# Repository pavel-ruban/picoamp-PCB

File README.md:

# straddle usb-c connector option (fork changes first 3 images):

pcb|top|bottom|pcb|3d|dev-pcb|dev-3d
--|--|--|--|--|--|--
||||||

* usb c connector https://aliexpress.com/item/1005003274837739.html
* push button soldered on top of the pcb to interact with steamvr dashboard
https://aliexpress.com/item/32622269899.html?sku_id=59394778361

# indexspeakerdacsmol

compact usb-i2s dac using rp2040 and max98360a for powering speakers, like index bmr drivers

* I forgot the silkscreen for usb pins, but they should be clear from below images.
* 0201 components suck to work with.
* intended to use with a usb-c cable, however the CC wire needs 5.1K pull-down to ground which I forgot about

firmware for the device is at https://github.com/sctanf/picoamp

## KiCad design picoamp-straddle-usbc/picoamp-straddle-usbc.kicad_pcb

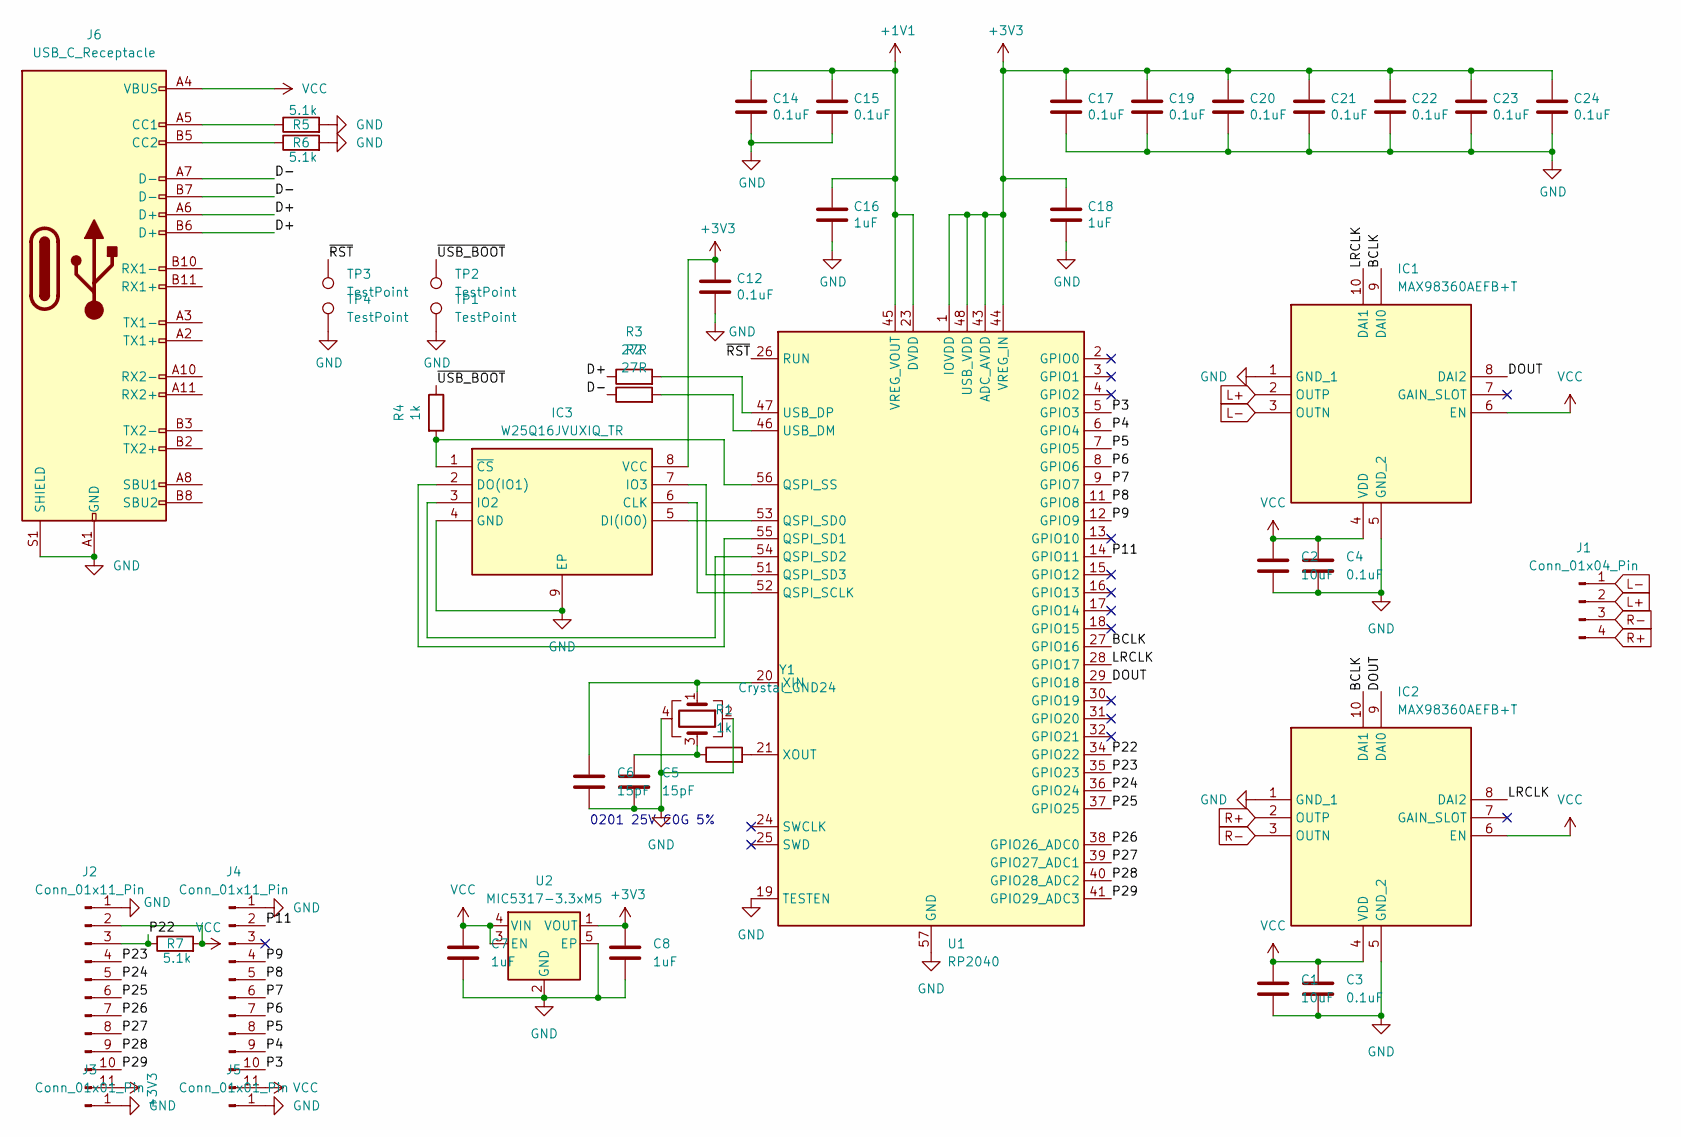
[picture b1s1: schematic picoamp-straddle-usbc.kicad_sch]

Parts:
C1, C2: 10uF; C_0603_1608Metric; Manufacturer_Part_Number GRM188C81A106MA73D; Mouser Part Number 81-GRM188C81A106MA3D
C3, C4: 0.1uF; C_0402_1005Metric; Manufacturer_Part_Number GRM155R61A104KA01J; Mouser Part Number 81-GRM15R61A104KA01J
C5, C6: 15pF; C_0201_0603Metric; Manufacturer_Part_Number GRM0335C1E150JA01D; Mouser Part Number 81-GRM0335C1E150JA1D
C7, C8, C16, C18: 1uF; C_0402_1005Metric; Manufacturer_Part_Number GRM155C81A105KA12J; Mouser Part Number 81-GRM155C81A105KA2J
C12, C14, C15, C17, C19, C20, C21, C22, C23, C24: 0.1uF; C_0201_0603Metric; Manufacturer_Part_Number GRM033C80J104KE15D; Mouser Part Number 81-GRM33C80J104KE15D
IC1, IC2: MAX98360AEFB+T; MAX98360AEFB; Mouser Part Number 700-MAX98360AEFB+T
IC3: W25Q16JVUXIQ_TR; SON50P300X200X60-9N; Mouser Part Number 454-W25Q16JVUXIQTR
J1: Conn_01x04_Pin; Pin
J2, J4: Conn_01x11_Pin; PinHeader_1x11_P2.00mm_Vertical
J3, J5: Conn_01x01_Pin; PinHeader_1x01_P2.00mm_Vertical
J6: USB_C_Receptacle; USB_C_Plug_Straddle
R1: 1k; R_0402_1005Metric; Manufacturer_Part_Number CRCW04021K00FKED; Mouser Part Number 71-CRCW0402-1.0K-E3
R2, R3: 27R; R_0201_0603Metric; Manufacturer_Part_Number RC0201FR-0727RL; Mouser Part Number 603-RC0201FR-0727RL
R4: 1k; R_0201_0603Metric; Manufacturer_Part_Number CR0201-FW-1001GLF; Mouser Part Number 652-CR0201FW-1001GLF
R5, R6, R7: 5.1k; R_0201_0603Metric; Manufacturer_Part_Number RC0201JR-075K1L; Mouser Part Number 603-RC0201JR-075K1L
TP1, TP2, TP3, TP4: TestPoint; TestPoint_Pad_1.0x1.0mm
U1: RP2040; QFN-56-1EP_7x7mm_P0.4mm_EP3.2x3.2mm; Manufacturer_Part_Number SC0914(7); Mouser Part Number 358-SC09147
U2: MIC5317-3.3xM5; UDFN-4-1EP_1x1mm_P0.65mm_EP0.48x0.48mm; Manufacturer_Part_Number MIC5317-3.3YMT-TR; Mouser Part Number 494-MIC531733YMTTR
Y1: Crystal_GND24; Crystal_SMD_3225-4Pin_3.2x2.5mm; Manufacturer_Part_Number ECS-120-10-33-AGM-TR; Mouser Part Number 520-120-10-33-AGMT

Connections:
+1V1: C14.1, C15.1, C16.1, U1.23 (DVDD), U1.45 (VREG_VOUT), U1.50 (DVDD)
+3V3: C8.1, C12.1, C17.1, C18.1, C19.1, C20.1, C21.1, C22.1, C23.1, C24.1, IC3.8 (VCC), J2.11, U1.1 (IOVDD), U1.10 (IOVDD), U1.22 (IOVDD), U1.33 (IOVDD), U1.42 (IOVDD), U1.43 (ADC_AVDD), U1.44 (VREG_IN), U1.48 (USB_VDD), U1.49 (IOVDD), U2.1 (VOUT)
/BCLK: IC1.9 (DAI0), IC2.10 (DAI1), U1.27 (GPIO16)
/D+: J6.A6 (D+), J6.B6 (D+), R3.1
/D-: J6.A7 (D-), J6.B7 (D-), R2.1
/DOUT: IC1.8 (DAI2), IC2.9 (DAI0), U1.29 (GPIO18)
/LRCLK: IC1.10 (DAI1), IC2.8 (DAI2), U1.28 (GPIO17)
/P3: J4.10, U1.5 (GPIO3)
/P4: J4.9, U1.6 (GPIO4)
/P5: J4.8, U1.7 (GPIO5)
/P6: J4.7, U1.8 (GPIO6)
/P7: J4.6, U1.9 (GPIO7)
/P8: J4.5, U1.11 (GPIO8)
/P9: J4.4, U1.12 (GPIO9)
/P11: J4.2, U1.14 (GPIO11)
/P22: J2.3, R7.1, U1.34 (GPIO22)
/P23: J2.4, U1.35 (GPIO23)
/P24: J2.5, U1.36 (GPIO24)
/P25: J2.6, U1.37 (GPIO25)
/P26: J2.7, U1.38 (GPIO26_ADC0)
/P27: J2.8, U1.39 (GPIO27_ADC1)
/P28: J2.9, U1.40 (GPIO28_ADC2)
/P29: J2.10, U1.41 (GPIO29_ADC3)
/~RST: TP3.1, U1.26 (RUN)
/~USB_BOOT: R4.1, TP2.1
GND: C1.2, C2.2, C3.2, C4.2, C5.2, C6.2, C7.2, C8.2, C12.2, C14.2, C15.2, C16.2, C17.2, C18.2, C19.2, C20.2, C21.2, C22.2, C23.2, C24.2, IC1.1 (GND_1), IC1.5 (GND_2), IC2.1 (GND_1), IC2.5 (GND_2), IC3.4 (GND), IC3.9 (EP), J2.1, J3.1, J4.1, J5.1, J6.A1 (GND), J6.A12 (GND), J6.B1 (GND), J6.B12 (GND), J6.S1 (SHIELD), R5.2, R6.2, TP1.1, TP4.1, U1.19 (TESTEN), U1.57 (GND), U2.2 (GND), U2.5 (EP), Y1.2, Y1.4
L+: IC1.2 (OUTP), J1.2
L-: IC1.3 (OUTN), J1.1
unnamed: C5.1, R1.1, Y1.3
unnamed: IC3.6 (CLK), U1.52 (QSPI_SCLK)
unnamed: IC3.5 (DI(IO0)), U1.53 (QSPI_SD0)
unnamed: IC3.2 (DO(IO1)), U1.55 (QSPI_SD1)
unnamed: IC3.3 (IO2), U1.54 (QSPI_SD2)
unnamed: IC3.7 (IO3), U1.51 (QSPI_SD3)
unnamed: IC3.1 (~CS), R4.2, U1.56 (QSPI_SS)
unnamed: J6.A5 (CC1), R5.1
unnamed: J6.B5 (CC2), R6.1
unnamed: R2.2, U1.46 (USB_DM)
unnamed: R3.2, U1.47 (USB_DP)
unnamed: C6.1, U1.20 (XIN), Y1.1
unnamed: R1.2, U1.21 (XOUT)
R+: IC2.2 (OUTP), J1.4
R-: IC2.3 (OUTN), J1.3
VCC: C1.1, C2.1, C3.1, C4.1, C7.1, IC1.4 (VDD), IC1.6 (EN), IC2.4 (VDD), IC2.6 (EN), J2.2, J4.11, J6.A4 (VBUS), J6.A9 (VBUS), J6.B4 (VBUS), J6.B9 (VBUS), R7.2, U2.3 (EN), U2.4 (VIN)

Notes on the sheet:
0201 25V C0G 5%

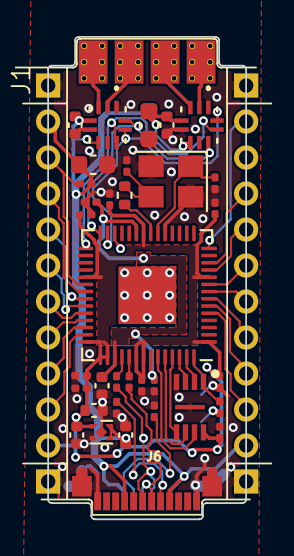
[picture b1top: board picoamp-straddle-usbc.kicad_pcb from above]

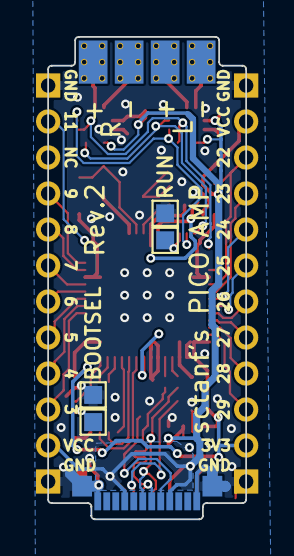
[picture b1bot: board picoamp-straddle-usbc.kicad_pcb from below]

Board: 2 copper layers, 11.0 x 26.8 mm, 43 parts (5 on the bottom side), 44 nets.

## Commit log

2024-06-11 Added USB C straddle connector & straight pins for speakers, also adjusted PCB to mount a PUSH button on top for gaze dot style interaction.
2024-06-12 Fix issue with 0201 components in the BOM file (0603 were chosen by jlcpcb auto tool by default).
